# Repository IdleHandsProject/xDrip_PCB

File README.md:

# xDrip_PCB

A custom PCB for the xDrip Project
<p>The xDrip project can be found here: http://stephenblackwasalreadytaken.github.io/xDrip/
Note: This board has not been tested. It is a WIP.
<p>Please don't go blindly ordering a board and expecting it to work. Go over the schematics yourself and confirm everything is correct. I will post an update when I have a working version.
<p>I am also working on a 3D printed case that will be available on shapeways, and I will be looking into mass producing the boards to reduce the costs. They will be fully completed boards. 
<p>I post updates on Twitter:  <a href="http://www.twitter.com/idlehandsdev">@idlehandsdev</a>

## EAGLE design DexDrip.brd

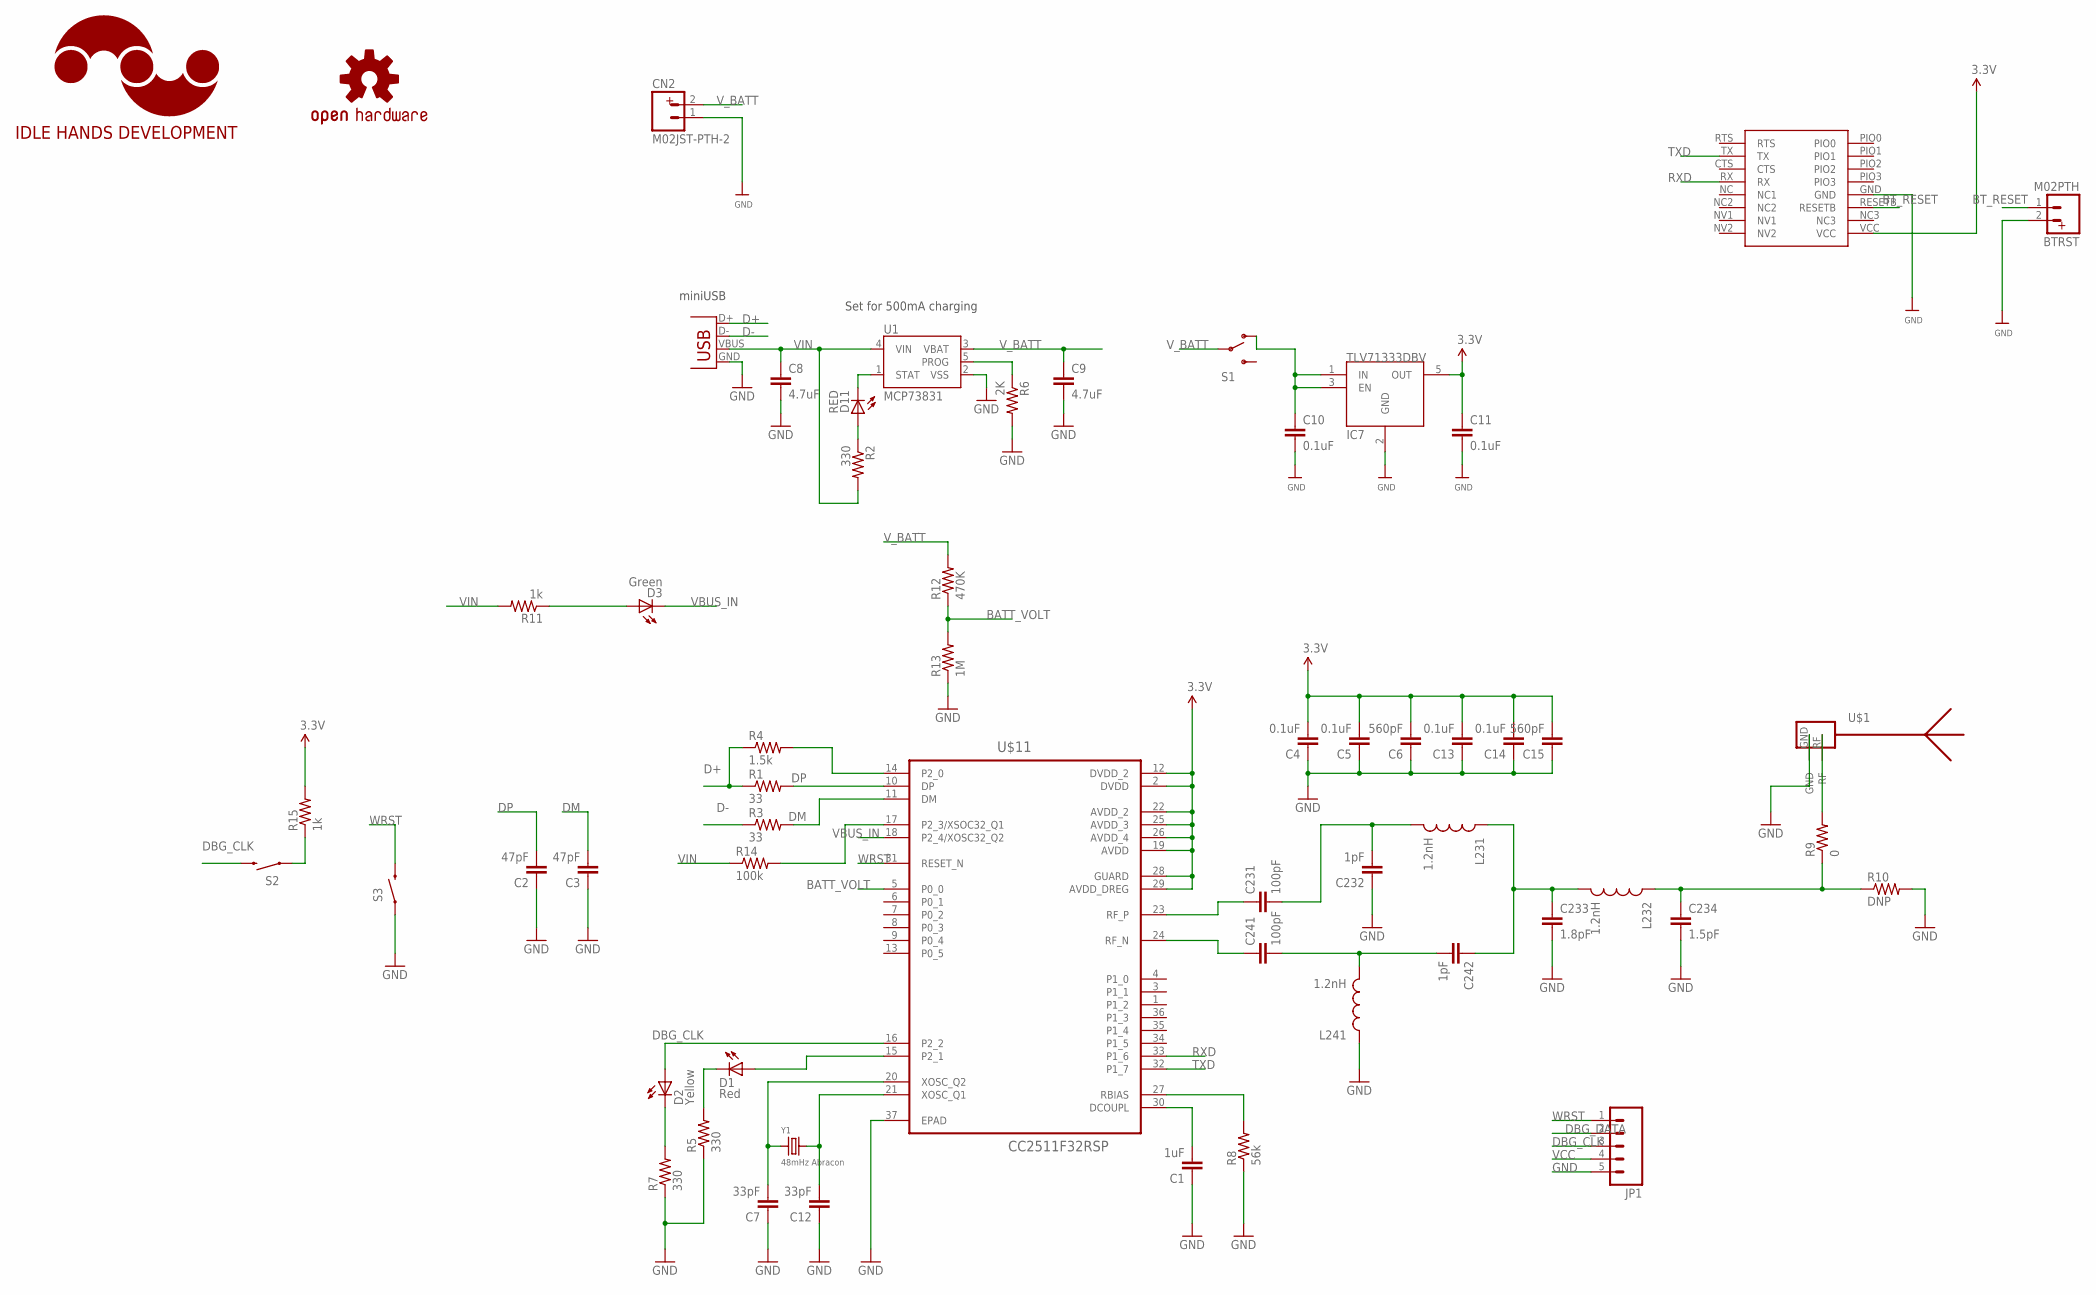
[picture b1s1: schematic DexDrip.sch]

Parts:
BTRST: M02PTH; 1X02
C1: 1uF; 0402-CAP
C2, C3: 47pF; 0402-CAP
C4, C5, C13, C14: 0.1uF; 0402-CAP
C6, C15: 560pF; 0402-CAP
C7, C12: 33pF; 0402-CAP
C8, C9: 4.7uF; 0402-CAP
C10, C11: 0.1uF; C0402
C231, C241: 100pF; 0402-CAP
C232, C242: 1pF; 0402-CAP
C233: 1.8pF; 0402-CAP
C234: 1.5pF; 0402-CAP
CN2: M02JST-PTH-2; JST-2-PTH
D1: Red; LED-0603
D2: Yellow; LED-0603
D3: Green; LED-0603
D11: RED; LED-0603
IC7: TLV71333DBV; SOT-23-5
JP1: M05LOCK; 1X05_LOCK
L231, L232, L241: 1.2nH; C0402
LOGO1: IDLEHANDS_LOGOS; IHD-LOGO-S
LOGO2: OSHW-LOGOS; OSHW-LOGO-S
R1, R3: 33; 0402-RES
R2, R5, R7: 330; 0402-RES
R4: 1.5k; 0402-RES
R6: 2K; 0402-RES
R8: 56k; 0402-RES
R9: 0; 0402-RES
R10: DNP; 0402-RES
R11, R15: 1k; 0402-RES
R12: 470K; 0402-RES
R13: 1M; 0402-RES
R14: 100k; 0402-RES
S1: SWITCH-SPDT-SMD-A; SWITCH-SPST-SMD-A
S2, S3: SWITCH-MOMENTARY-2-SMD-1101NE; TACTILE-SWITCH-1101NE
U1: MCP73831; SOT23-5
U$1: ANTENNA_1LEFT; SWRA117D_LEFT
U$2: BT_HM11; HM11
U$11: CC2511F32RSP; QFN50P600X600X90-37N
X1: Micro USB; USB-MICROB
Y1: 48mHz Abracon; 3.2X2.5MM

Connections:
BATT_VOLT: R12.1, R13.2, U$11.5 (P0_0)
BT_RESET: BTRST.1, U$2.RESETB
D+: R1.1, R4.1, X1.D+
D-: R3.1, X1.D-
DBG_CLK: D2.A, JP1.3, S2.P$2 (2), U$11.16 (P2_2)
DBG_DATA: D1.A, JP1.2, U$11.15 (P2_1)
DM: C3.2, R3.2, U$11.11 (DM)
DP: C2.2, R1.2, U$11.10 (DP)
GND: BTRST.2, C1.1, C2.1, C3.1, C4.1, C5.1, C6.1, C7.1, C8.2, C9.2, C10.2, C11.2, C12.1, C13.1, C14.1, C15.1, C232.1, C233.2, C234.2, CN2.1, IC7.2 (GND), JP1.5, L241.1, R5.1, R6.2, R7.1, R8.1, R10.2, R13.1, S3.P$1 (1), U1.2 (VSS), U$1.GND, U$2.GND, U$11.37 (EPAD), X1.GND
unnamed: R4.2, U$11.14 (P2_0)
unnamed: D3.A, R11.1
unnamed: R9.2, U$1.RF
unnamed: R8.2, U$11.27 (RBIAS)
unnamed: C1.2, U$11.30 (DCOUPL)
unnamed: C10.1, IC7.1 (IN), IC7.3 (EN), S1.1 (O)
unnamed: R14.2, U$11.17 (P2_3/XSOC32_Q1)
unnamed: R15.1, S2.P$1 (1)
unnamed: D1.C, R5.2
unnamed: D11.A, R2.1
unnamed: D2.C, R7.2
unnamed: C7.2, U$11.20 (XOSC_Q2), Y1.1
unnamed: C12.2, U$11.21 (XOSC_Q1), Y1.3 (2)
unnamed: C231.1, U$11.23 (RF_P)
unnamed: C231.2, C232.2, L231.2
unnamed: C241.1, U$11.24 (RF_N)
unnamed: C241.2, C242.2, L241.2
unnamed: C233.1, C242.1, L231.1, L232.2
unnamed: C234.1, L232.1, R9.1, R10.1
PROG: R6.1, U1.5 (PROG)
RXD: U$2.RX, U$11.33 (P1_6)
STAT: D11.C, U1.1 (STAT)
TXD: U$2.TX, U$11.32 (P1_7)
VBUS_IN: D3.C, U$11.18 (P2_4/XOSC32_Q2)
VCC: C4.2, C5.2, C6.2, C11.1, C13.2, C14.2, C15.2, IC7.5 (OUT), JP1.4, R15.2, U$2.VCC, U$11.2 (DVDD), U$11.12 (DVDD_2), U$11.19 (AVDD), U$11.22 (AVDD_2), U$11.25 (AVDD_3), U$11.26 (AVDD_4), U$11.28 (GUARD), U$11.29 (AVDD_DREG)
VIN: C8.1, R2.2, R11.2, R14.1, U1.4 (VIN), X1.VBUS
V_BATT: C9.1, CN2.2, R12.2, S1.2, U1.3 (VBAT)
WRST: JP1.1, S3.P$2 (2), U$11.31 (RESET_N)

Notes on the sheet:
Set for 500mA charging
miniUSB

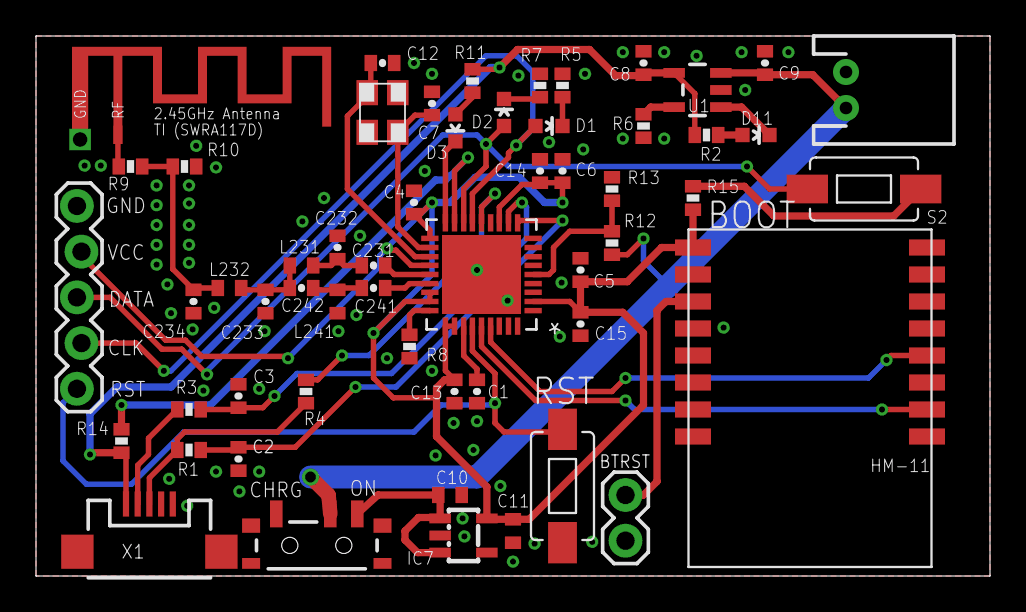
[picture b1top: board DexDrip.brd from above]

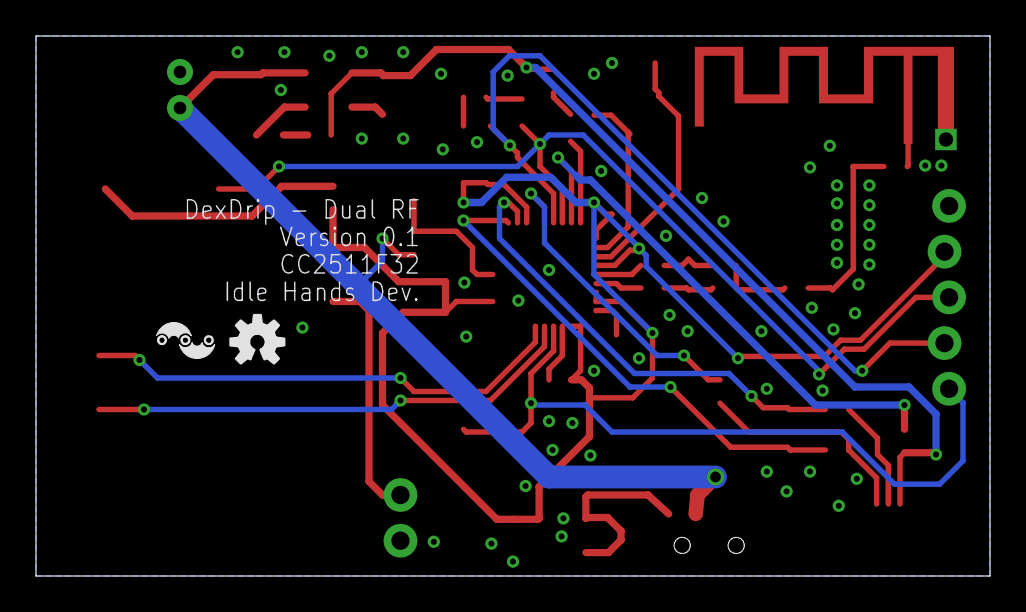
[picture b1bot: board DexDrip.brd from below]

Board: 2 copper layers, 53.0 x 30.0 mm, 58 parts (2 on the bottom side), 37 nets.

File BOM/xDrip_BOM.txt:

Qty	Value	Device	Package	Parts	Description	PROD_ID
						
1		SWITCH-SPDT-SMD-A	SWITCH-SPST-SMD-A	S1	SPDT Switch	563-1102-1-ND
6	0.1uF	C-EUC0402	C0402	"C4, C5, C13, C14, C10, C11"	"CAPACITOR, European symbol"	587-1227-1-ND
3	1.2nH	INDUCTOR0402	C0402	"L231, L232, L241"	Inductors	587-1499-1-ND
1	1.5k	RESISTOR0402-RES	0402-RES	R4	Resistor	P1.50KLCT-ND
1	1.5pF	.1UF-CER	0402-CAP	C234	.1uF ceramic SMT	490-6213-1-ND
1	1.8pF	.1UF-CER	0402-CAP	C233	.1uF ceramic SMT	712-1271-1-ND
1	100k	RESISTOR0402-RES	0402-RES	R14	Resistor	P100KJCT-ND
2	100pF	.1UF-CER	0402-CAP	"C231, C241"	.1uF ceramic SMT	490-5922-1-ND
1	1M	RESISTOR0402-RES	0402-RES	R13	Resistor	P1.00MLCT-ND
1	1k	RESISTOR0402-RES	0402-RES	R11	Resistor	P1.0KJCT-ND
2	1pF	.1UF-CER	0402-CAP	"C232, C242"	.1uF ceramic SMT	587-1007-1-ND
1	1uF	.1UF-CER	0402-CAP	C1	.1uF ceramic SMT	490-1320-1-ND
1	2K	RESISTOR0402-RES	0402-RES	R6	Resistor	P2.00KLCT-ND
2	33	RESISTOR0402-RES	0402-RES	"R1, R3"	Resistor	P33.0LCT-ND
6	330	RESISTOR0402-RES	0402-RES	"R2, R5, R7, R9, R10, R15"	Resistor	RMCF0402JT330RCT-ND
2	33pF	.1UF-CER	0402-CAP	"C7, C12"	.1uF ceramic SMT	490-5936-1-ND
2	4.7uF	CAP0402-CAP	0402-CAP	"C8, C9"	Capacitor	490-5915-1-ND
1	470K	RESISTOR0402-RES	0402-RES	R12	Resistor	RHM470KCDCT-ND
2	47pF	.1UF-CER	0402-CAP	"C2, C3"	.1uF ceramic SMT	399-7796-1-ND
1	48mHz Abracon	CRYSTAL.3.2X2.5MM	3.2X2.5MM	Y1		535-10282-1-ND
2	560pF	.1UF-CER	0402-CAP	"C6, C15"	.1uF ceramic SMT	1276-1577-1-ND
1	56k	RESISTOR0402-RES	0402-RES	R8	Resistor	RHM56.0KCDCT-ND
1	CC2511F32RSP	CC2511F32RSP	QFN50P600X600X90-37N	U$11		296-22557-1-ND
1	Green	LED0603	LED-0603	D3	LEDs	160-1446-1-ND
1	M02JST-PTH-2	M02JST-PTH-2	JST-2-PTH	CN2	"Standard 2-pin 0.1 header. Use with"""	455-1719-ND
1	MCP73831	MCP73831	SOT23-5	U1	Microchip's MCP73831	MCP73831T-2ACI/OTCT-ND
1	Micro USB	USB-MICROB	USB-MICROB	X1	USB Connectors	609-4053-1-ND
2	RED	LED0603	LED-0603	"D1, D11"	LEDs	160-1445-1-ND
2	SWITCH-MOMENTARY-2-SMD-1101NE	SWITCH-MOMENTARY-2-SMD-1101NE	TACTILE-SWITCH-1101NE	"S2, S3"	"Various NO switches- pushbuttons, reed, etc"	311-270JRCT-ND
1	TLV71333DBV	TLV71333DBV	SOT-23-5	IC7	"Capacitor-Free, 150-mA, Low-Dropout Regulator"	296-35591-1-ND
1	Yellow	LED0603	LED-0603	D2	LEDs	160-1445-1-ND

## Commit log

2015-06-04 First Upload
2015-06-09 Added programming pins
2015-06-09 Added BOM
2015-06-12 Fixed button part number
2015-06-12 Fixes some R Values RF WORKING
2015-06-12 words moved

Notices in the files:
parts and their libraries:
SparkFun-Connectors: Licensing: CC v3.0 Share-Alike You are welcome to use this library for commercial purposes.
